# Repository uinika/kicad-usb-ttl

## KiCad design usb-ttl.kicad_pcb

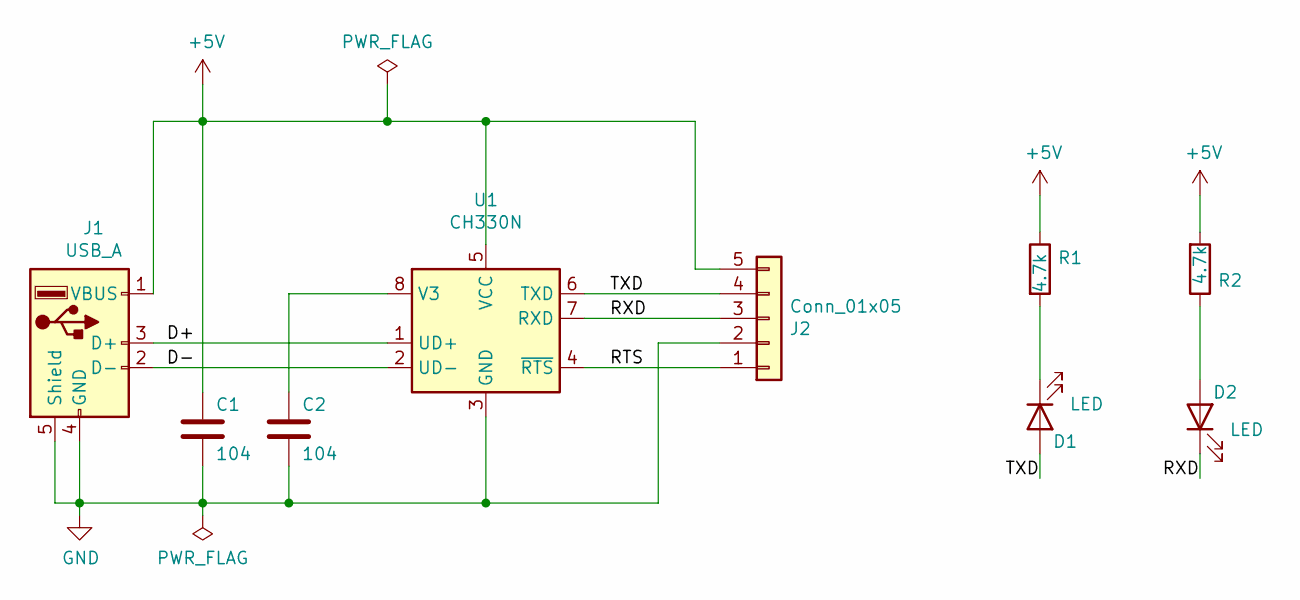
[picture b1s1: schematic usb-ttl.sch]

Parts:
C1, C2: 104; C_0603_1608Metric
D1, D2: LED; LED_0603_1608Metric
J1: USB_A; USB_A_CNCTech_1001-011-01101_Horizontal
J2: Conn_01x05; PinHeader_1x05_P2.54mm_Horizontal
R1, R2: 4.7k; R_0603_1608Metric
U1: CH330N; SOIC-8_3.9x4.9mm_P1.27mm

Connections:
+5V: C1.1, J1.1 (VBUS), J2.5, R1.1, R2.2, U1.5 (VCC)
/D+: J1.3 (D+), U1.1 (UD+)
/D-: J1.2 (D-), U1.2 (UD-)
/RTS: J2.1, U1.4 (~RTS)
/RXD: D2.1 (K), J2.3, U1.7 (RXD)
/TXD: D1.2 (A), J2.4, U1.6 (TXD)
GND: C1.2, C2.2, J1.4 (GND), J1.5 (Shield), J2.2, U1.3 (GND)
unnamed: C2.1, U1.8 (V3)
unnamed: D1.1 (K), R1.2
unnamed: D2.2 (A), R2.1

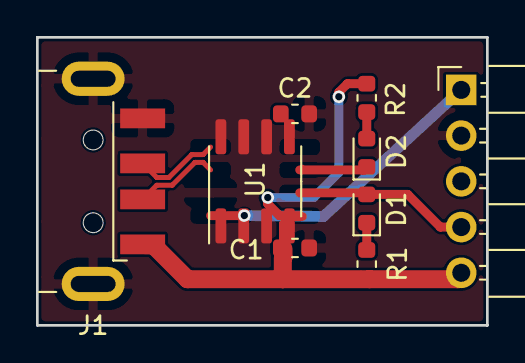
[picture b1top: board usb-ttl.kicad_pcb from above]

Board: 2 copper layers, 25.0 x 16.0 mm, 9 parts (0 on the bottom side), 10 nets.
